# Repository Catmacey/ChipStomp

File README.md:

ChipStomp Guitar Effects Pedal
==============================

This is a digital guitar effects pedal based on the Arduino compatible Chipkit DP32 platform.
The project is a merging of a ChipKit DP32 with an Open Music Labs Stompshield in a custom build PCB.

The Chipkit is an arduino compatible platform powered by a 32bit Microchip PIC processor running at 40Mhz with 32Kb RAM and 128Kb flash.  

UPDATE: There is a [3d printable case available for this project](https://github.com/Catmacey/ChipStompCase). 

The project is relatively simple in that it limits itself to using the PIC's internal RAM, built in 10bit ADC and utilizes two 8bit PWMs to form a single 16bit output.  Also included is a 128x64px 1.3" OLED to provide a nice user interface.

Currently the following effects are completed.
- **Flanger** : Classic wobbly tape effect.

- **Tremolo** : Low frequency modulation of the source audio.

- **Pitch shift** : Change the pitch (up or down) of the source audio without changing the playback speed.

- **Echo/Delay** : A simple lo-fi delay (700ms Max) that when combined with a bit of analogue feedback provides a nice echo.

- **Bitcrusher** : Reduces the sample rate by ratios down to 1/64 of the source rate, also reduces the bit-depth to create some nice messy sounds.

You can have all or just some of these effect running at the same time with each passing its output onto the next effects input. 

[More information is available on my blog.](http://catmacey.wordpress.com/tag/chipstomp/)

Copyright (C) 2014 Matt Casey : catmacey.com
This program is free software: you can redistribute it and/or modify it under the terms of the GNU General Public License as published by the Free Software Foundation, either version 3 of the License, or (at your option) any later version.
	
This program is distributed in the hope that it will be useful, but WITHOUT ANY WARRANTY; without even the implied warranty of MERCHANTABILITY or FITNESS FOR A PARTICULAR PURPOSE.  See the GNU General Public License for more details.

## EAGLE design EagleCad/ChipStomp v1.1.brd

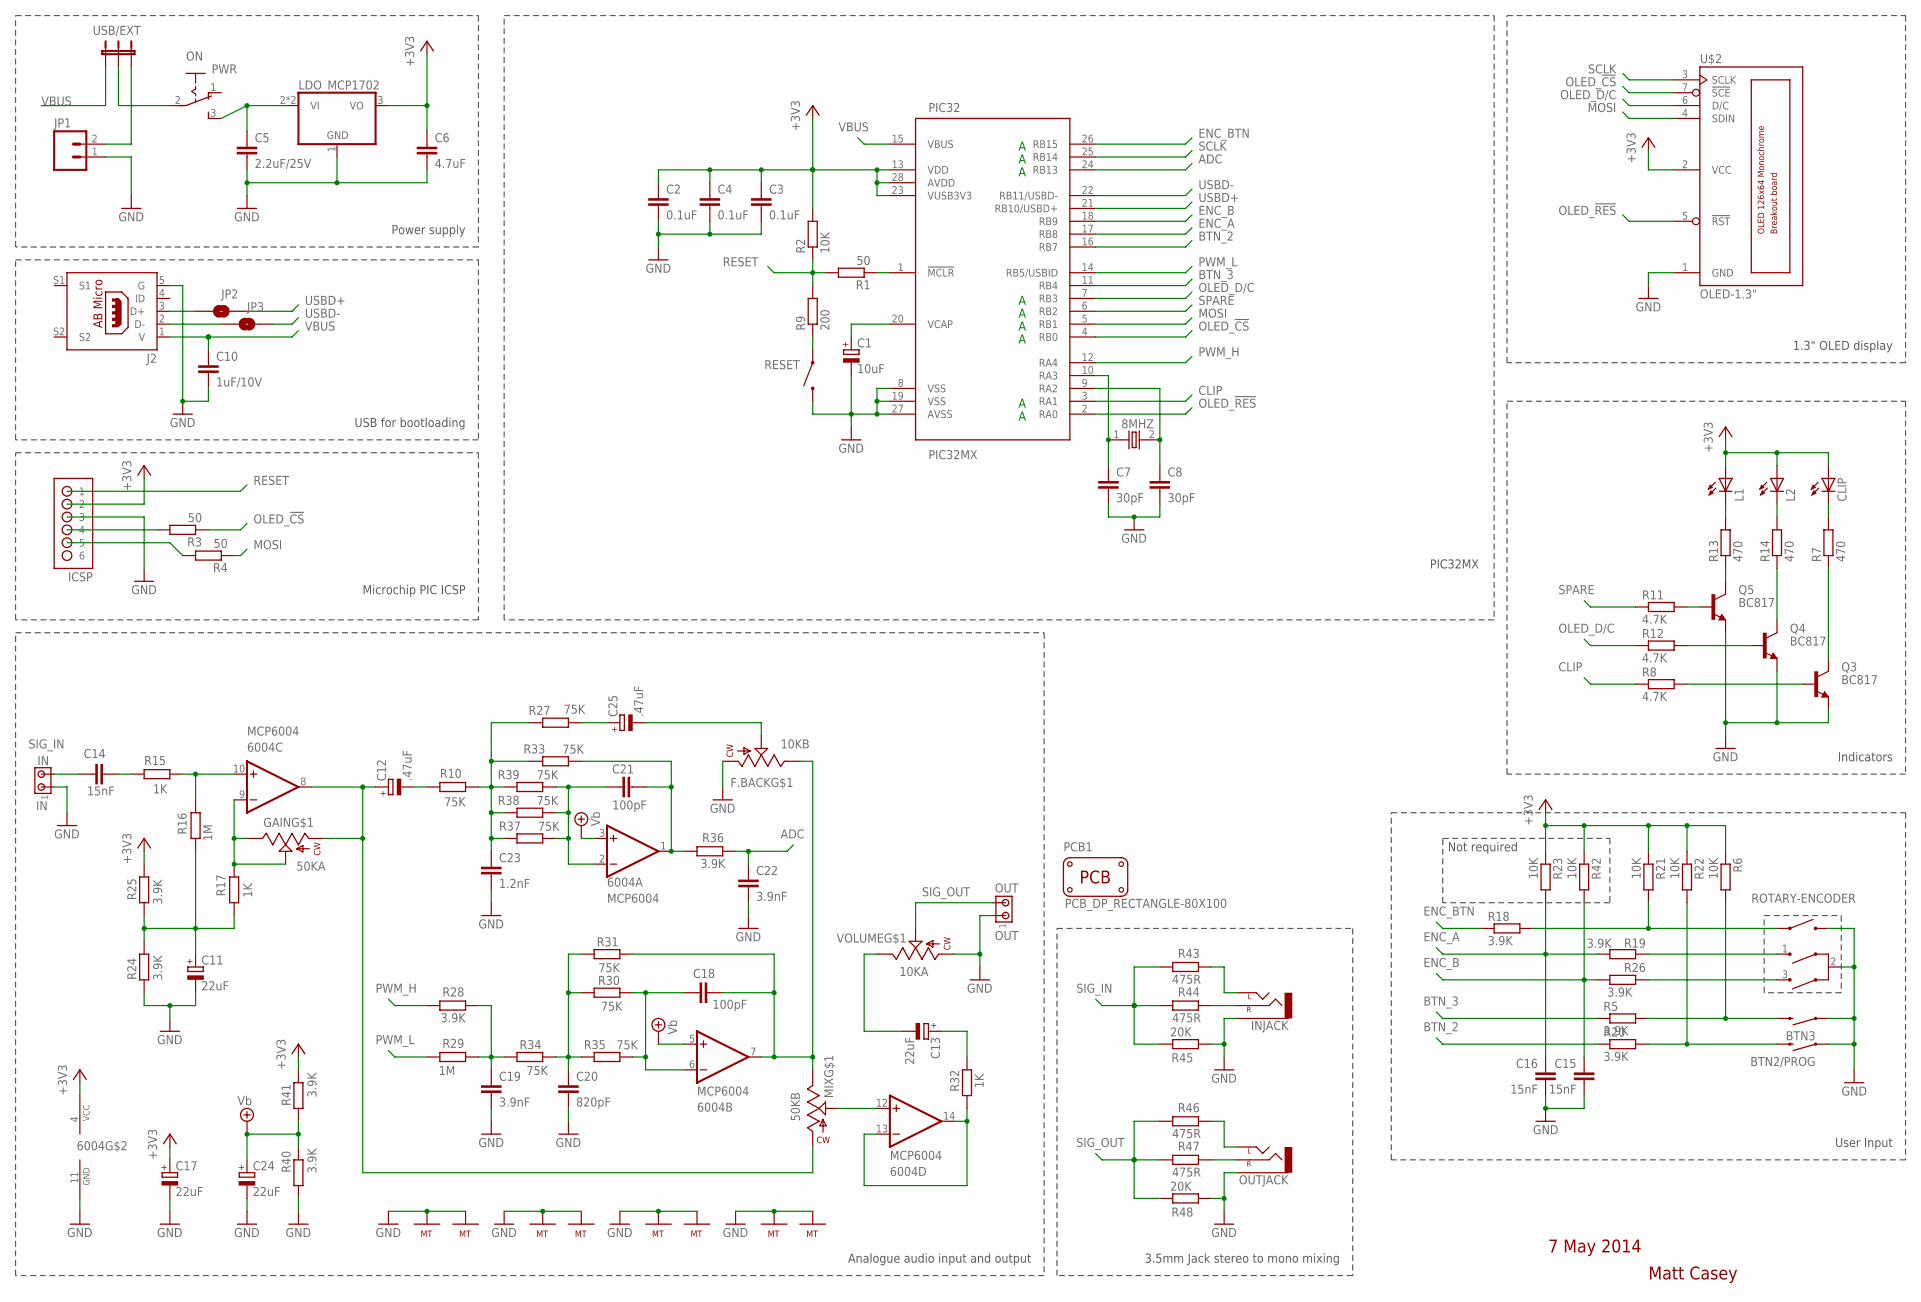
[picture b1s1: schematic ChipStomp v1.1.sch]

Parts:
8MHZ: OSC-XTAL-HC-49U-SMD; HC-49U
6004: MCP6004; SO-14
BTN2/PROG, BTN3: SWITCH-MOMENTARY-212MM; TACTILE-PTH-12MM
C1: 10uF; A/3216-18R
C2, C3, C4: 0.1uF; C0805K
C5: 2.2uF/25V; C0805K
C6: 4.7uF; C0805K
C7, C8: 30pF; C0805K
C10: 1uF/10V; C0805K
C11, C13, C17, C24: 22uF; 153CLV-0505
C12, C25: .47uF; 153CLV-0405
C14, C15, C16: 15nF; C0805K
C18, C21: 100pF; C0805K
C19, C22: 3.9nF; C0805K
C20: 820pF; C0805K
C23: 1.2nF; C0805K
CLIP: LED-0805; LED-805
F.BACK: 10KB; POT/SINGLE/PANASONIC/VERT
GAIN: 50KA; POT/SINGLE/PANASONIC/VERT
ICSP: No Load; HDR-1X6_OFFSET
IN: IN; JMP/2P/SIP
INJACK: AUDIO-JACKPTH; STEREO_JACK3.5MM_PTH
J2: US-AB-MICRO-TH; WMRU2AB-05FLB2DSR-4.0
JP1: M023.5MM; SCREWTERMINAL-3.5MM-2
JP2, JP3: Straight Male; SJ_2S-TRACE
L1, L2: LED-0805; LED-805
MIX: 50KB; POT/SINGLE/PANASONIC/VERT
ON: PWR; DX_MINI_SPDT_VERTICAL
OUT: OUT; JMP/2P/SIP
OUTJACK: AUDIO-JACKPTH; STEREO_JACK3.5MM_PTH
PCB1: PCB_DP_RECTANGLE-80X100; DP10080_V1
PIC32: PIC32MX; SO-28
Q3, Q4, Q5: BC817; SOT23-BEC
R1, R3, R4: 50; R0805
R2, R6, R21, R22, R23, R42: 10K; R0805
R5, R18, R19, R20, R24, R25, R26, R28, R36, R40, R41: 3.9K; R0805
R7, R13, R14: 470; R0805
R8, R11, R12: 4.7K; R0805
R9: 200; R0805
R10, R27, R30, R31, R33, R34, R35, R37, R38, R39: 75K; R0805
R15, R17, R32: 1K; R0805
R16, R29: 1M; R0805
R43, R44, R46, R47: 475R; R0805
R45, R48: 20K; R0805
RESET: TINY_TACTILEPTH; TINY_TACTILE_PTH
SW1: ROTARY-ENCODER; SURE
U$2: OLED-1.3"; OLED-130-BREAKOUT_2HOLES
U$3: LDO_MCP1702; SOT89
USB/EXT: JUMPER-3PTH; 1X03
VOLUME: 10KA; POT/SINGLE/PANASONIC/VERT

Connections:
+3V3: 6004.4 (VCC), C2.1, C3.1, C4.1, C6.1, C17.+, CLIP.A, ICSP.2, L1.A, L2.A, PIC32.13 (VDD), PIC32.23 (VUSB3V3), PIC32.28 (AVDD), R2.2, R6.1, R21.1, R22.1, R23.1, R25.1, R41.1, R42.1, U$2.2 (VCC), U$3.3 (VO)
ADC: C22.1, PIC32.24 (RB13), R36.1
BTN_2: PIC32.16 (RB7), R20.1
BTN_3: PIC32.11 (RB4), R5.1
CLIP: PIC32.3 (RA1), R8.1
ENC_A: C16.1, PIC32.17 (RB8), R19.1, R23.2
ENC_B: C15.1, PIC32.18 (RB9), R26.1, R42.2
ENC_BTN: PIC32.26 (RB15), R18.1
GND: 6004.11 (GND), BTN2/PROG.1, BTN3.1, C1.-, C2.2, C3.2, C4.2, C5.2, C6.2, C7.2, C8.2, C10.2, C11.-, C15.2, C16.2, C17.-, C19.2, C20.2, C22.2, C23.2, C24.-, F.BACK.P$1 (1), F.BACK.P$4 (MT), F.BACK.P$5 (MT), GAIN.P$4 (MT), GAIN.P$5 (MT), ICSP.3, IN.1, INJACK.S (SLEEVE), INJACK.S@1 (SLEEVE), J2.5 (G), JP1.1, MIX.P$4 (MT), MIX.P$5 (MT), OUT.1, OUTJACK.S (SLEEVE), OUTJACK.S@1 (SLEEVE), PIC32.8 (VSS), PIC32.19 (VSS), PIC32.27 (AVSS), Q3.E, Q4.E, Q5.E, R24.2, R40.2, R45.2, R48.2, RESET.2 (B), SW1.2 (COMMON), SW1.A (B), U$2.1 (GND), U$3.1 (GND), VOLUME.P$1 (1), VOLUME.P$4 (MT), VOLUME.P$5 (MT)
MOSI: PIC32.5 (RB1), R4.1, U$2.4 (SDIN)
unnamed: PIC32.1 (!MCLR), R1.1
unnamed: BTN3.3 (2), R5.2, R6.2
unnamed: Q3.C, R7.1
unnamed: Q3.B, R8.2
unnamed: CLIP.C, R7.2
unnamed: INJACK.L (LEFT), INJACK.L@1 (LEFT), R43.1
unnamed: INJACK.R (RIGHT), R44.1
unnamed: ON.2, USB/EXT.2
unnamed: OUTJACK.L (LEFT), OUTJACK.L@1 (LEFT), R46.1
unnamed: R9.1, RESET.1 (A)
unnamed: C1.+, PIC32.20 (VCAP)
unnamed: OUTJACK.R (RIGHT), R47.1
unnamed: C14.2, R15.2
unnamed: JP1.2, USB/EXT.3
unnamed: 6004.10 (+IN), R15.1, R16.2
unnamed: Q5.B, R11.2
unnamed: Q5.C, R13.1
unnamed: Q4.C, R14.1
unnamed: Q4.B, R12.2
unnamed: 6004.8 (OUT), C12.+, GAIN.P$1 (1), MIX.P$1 (1)
unnamed: J2.2 (D-), JP3.1
unnamed: 6004.9 (-IN), GAIN.P$2 (2), GAIN.P$3 (3), R17.2
unnamed: L1.C, R13.2
unnamed: L2.C, R14.2
unnamed: C12.-, R10.2
unnamed: R18.2, R21.2, SW1.B (A)
unnamed: BTN2/PROG.3 (2), R20.2, R22.2
unnamed: C23.1, R10.1, R27.2, R33.2, R37.2, R38.2, R39.2
unnamed: 6004.2 (-IN), C21.1, R37.1, R38.1, R39.1
unnamed: 6004.1 (OUT), C21.2, R33.1, R36.2
unnamed: C11.+, R16.1, R17.1, R24.1, R25.2
unnamed: C19.1, R28.1, R29.1, R34.2
unnamed: C20.1, R30.2, R31.2, R34.1, R35.2
unnamed: 6004.6 (-IN), C18.1, R30.1, R35.1
unnamed: C25.+, R27.1
unnamed: 6004.7 (OUT), C18.2, F.BACK.P$3 (3), MIX.P$3 (3), R31.1
unnamed: C13.+, R32.1
unnamed: C13.-, VOLUME.P$3 (3)
unnamed: R19.2, SW1.1 (SIG1)
unnamed: R26.2, SW1.3 (SIG2)
unnamed: C25.-, F.BACK.P$2 (2)
unnamed: 6004.12 (+IN), MIX.P$2 (2)
unnamed: 6004.13 (-IN), 6004.14 (OUT), R32.2
OLED_!CS: PIC32.4 (RB0), R3.1, U$2.7 (!SCE)
OLED_!RES: PIC32.2 (RA0), U$2.5 (!RST)
OLED_D/C: PIC32.7 (RB3), R12.1, U$2.6 (D/C)
OSC1/CLKI/RPA2/RA2: 8MHZ.2, C8.1, PIC32.9 (RA2)
OSC2/CLKO/RPA3/PMA0/RA3: 8MHZ.1, C7.1, PIC32.10 (RA3)
PGC: ICSP.5, R4.2
PGD: ICSP.4, R3.2
PWM_H: PIC32.12 (RA4), R28.2
PWM_L: PIC32.14 (RB5/USBID), R29.2
RESET: ICSP.1, R1.2, R2.1, R9.2
SCLK: PIC32.25 (RB14), U$2.3 (SCLK)
SIG_IN: C14.1, IN.2, R43.2, R44.2, R45.1
SIG_OUT: OUT.2, R46.2, R47.2, R48.1, VOLUME.P$2 (2)
SPARE: PIC32.6 (RB2), R11.1
USBD+: J2.3 (D+), JP2.1, JP2.2, PIC32.21 (RB10/USBD+)
USBD-: JP3.2, PIC32.22 (RB11/USBD-)
VBUS: C10.1, J2.1 (V), PIC32.15 (VBUS), USB/EXT.1
VIN: C5.1, ON.3 (S), U$3.2 (VI), U$3.4 (VI)
VREF: 6004.3 (+IN), 6004.5 (+IN), C24.+, R40.1, R41.2

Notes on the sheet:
User Input
Power supply
Indicators
3.5mm Jack stereo to mono mixing
Analogue audio input and output
USB for bootloading
Microchip PIC ICSP
1.3" OLED display
Matt Casey
PIC32MX
7 May 2014
Not required

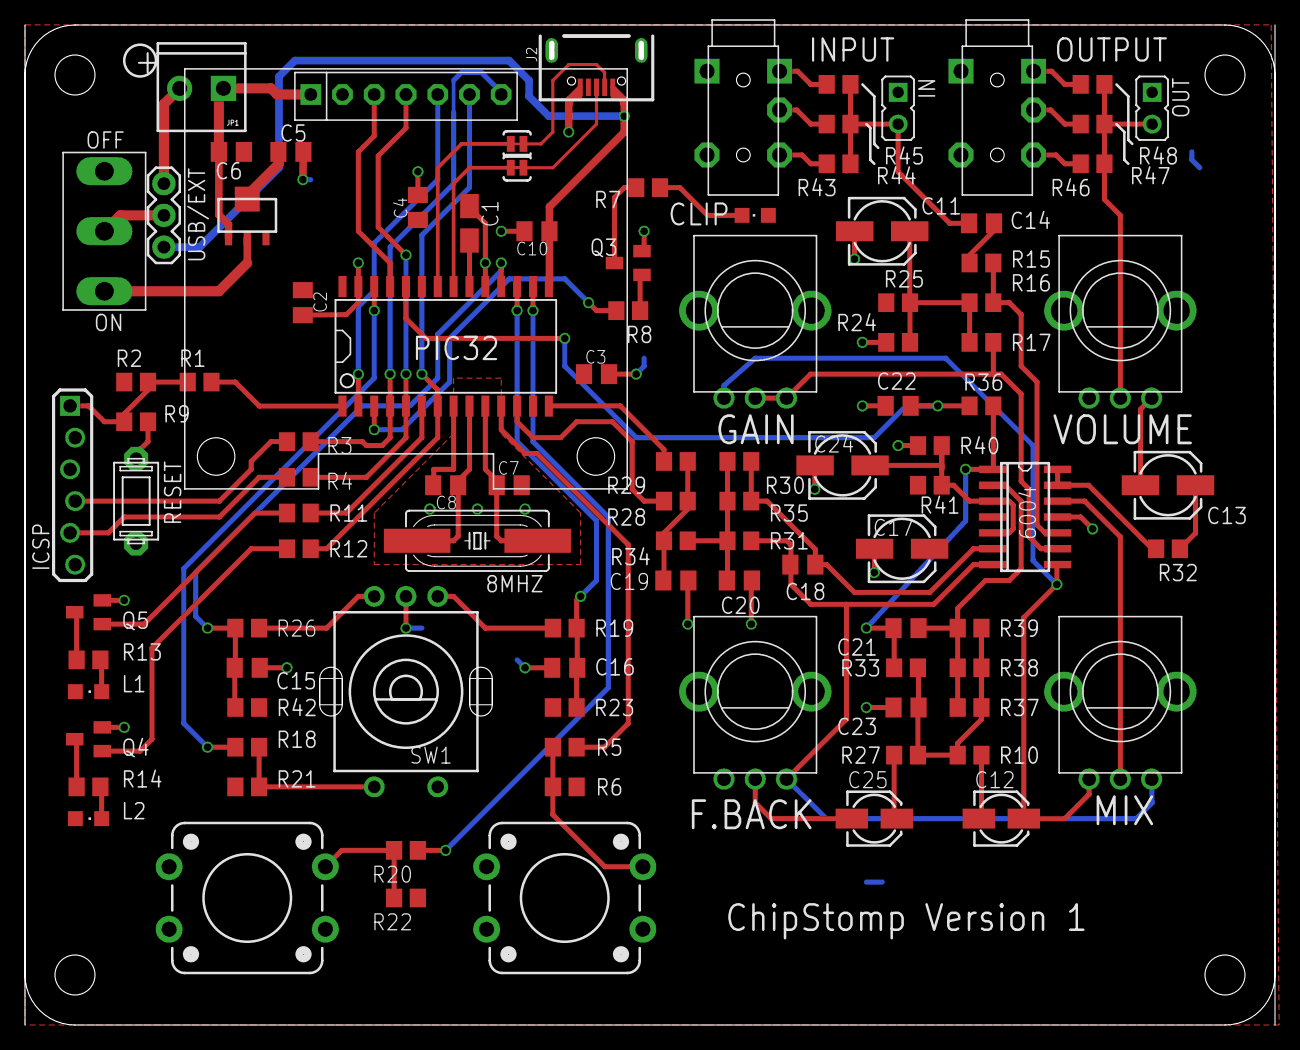
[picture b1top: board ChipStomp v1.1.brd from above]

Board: 2 copper layers, 100.0 x 80.0 mm, 103 parts (0 on the bottom side), 72 nets.

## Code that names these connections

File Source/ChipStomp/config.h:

/*
	Main header file
*/

#ifndef __Config__
#define __Config__

#include <stdint.h> 

// #define SAMPLERATE 44100    // Hz
// #define SAMPLETIME 0.02267 // Approx sample time in mS 
#define SAMPLERATE 40000
#define SAMPLETIME 0.025
// #define SAMPLERATE 32000  
// #define SAMPLETIME 0.03125
#define CLIPLEVEL 31000  // Full range is +32767 to -32767 but this is the level we light the LED at.
#define CLIPHARD 32767

// PIC port/pins
// PORT A
#define OLEDRES_BIT BIT_0  // RA0
#define CLIP_BIT    BIT_1  // RA1
// BIT_2 Osc
// BIT_3 Osc
#define DACHI_BIT   BIT_4  // RA4

// PORT B
// Outputs
#define OLEDCS_BIT  BIT_0
#define MOSI_BIT    BIT_1   // RB1
// BIT_2 Spare
#define OLEDDC_BIT  BIT_3   // RB3
#define DACLO_BIT   BIT_5   // RA5
#define SCLK_BIT    BIT_14

// Inputs
#define BTNSELECT_BIT BIT_4 // RB4
#define BTNEFFECT_BIT BIT_7 // RB7
#define ENCA_BIT BIT_8 // RB8
#define ENCB_BIT BIT_9 // RB9
#define ENCBTN_BIT BIT_15 // RB15

#define ENC_MASK ENCA_BIT | ENCB_BIT // Mask for encoder inputs
#define BTN_MASK BTNEFFECT_BIT | BTNSELECT_BIT | ENCBTN_BIT // Mask for buttons
#define INPUT_MASK ENC_MASK | BTN_MASK // Mask for all inputs

#define VUTICKLEN 16
#define VUTICKLEN_MASK 0x0f

// Some handy values for screen layout
#define DISP_FEAT_Y 20  // Start point for features area
#define DISP_FEAT_W 123 // MAx width of features area (allowing space for VU meter)
#define DISP_FEAT_INDENT 2  // Start point for features area

// Stupid Arduino pin numbers
#define OLED_RESET 9 // RA0 
#define DACL 0 // RB5 DAC Low byte
#define DACH 18 // RA4 DAC High byte
#define SPI_CLK 7 // RB14
#define OLED_CS 11 // RB0
#define OLED_DC 14 // RB3
#define SPI_MOSI 12 // RB1
#define _DSPI1_MOSI_PIN   12
// End of stupid Arduino pin numbers

#define SYS_FREQ 40000000 // PIC OSC frequency
#define GetSystemClock() SYS_FREQ
#define GetPeripheralClock()    (GetSystemClock() / (1 << OSCCONbits.PBDIV))

// This is used to store button state
// The Port the buttons are on is 16bit but the 
// in our case all the buttons are on the lower byte
typedef union {
  uint8_t complete;
  struct {
    unsigned :4;
    unsigned select:1;
    unsigned :1;
    unsigned :1;
    unsigned effect:1;
  };
} ButtonState_t;

// This is used to store the input
typedef struct {
  struct {
    int16_t value; // Accumulated value of encoder input. Set to 0 once actioned
    uint8_t state; // Current state, used in ISR decoding
  } encoder;
  ButtonState_t btn_state; // 1 = pressed
  ButtonState_t btn_diff; // 1 = different from last time
  uint32_t btn_timer; // Could use this to determine how long since last input...
} InputState_t;

// This is used to store the input and output VU Meter
typedef struct {
  int16_t input[VUTICKLEN];
  int16_t output[VUTICKLEN];
  uint8_t peak_in;
  uint8_t peak_out;
  uint8_t tick;
} VUMeter_t;


// Sinewave : 1024 value array of signed 16bit integers
const int16_t g_sinewave[] = {
  #include <sinetable.inc>
};

// Splash screen
const uint8_t g_splashscreen[] = {
  #include <splashscreen.inc>
};


// Returns the percentage value of value between the min and max range
extern float percentage(uint16_t value, uint16_t max, uint16_t min);

#endif

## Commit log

2014-05-29 Initial project creation.
    First upload of project description and Eagle Cad schematics and board
    layout
2014-05-29 Improved project readme
2014-05-29 Fixed broken markup
2014-09-28 First upload of Source code and libraries.
2014-09-29 Updated readme
    Provided a bit more info about the project in the readme.
2014-10-10 Added bootloader HEX
    Added compiled HEX of the ChipStomp specific bootloader.
    It's a modified Chipkit DP32 bootloader with the buttons configured as
    pulled high - active low, rather than pulled low - active high.
    Also added the BoardConfig.h from the Chipkit bootloader project
    modified to include the Chipstomp board definition.
2014-11-16 Added licence text to readme
2015-03-25 Changed sample rate to 40k
    Also a few updates to comments and minor changes.
2015-10-08 Updated to use multi-font GFX lib
    Modified as an example of using newly modified GFX lib to display two
    different fonts. DejaVuSans 12 for headers and LiberationSans 10 for
    body.

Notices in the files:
parts and their libraries:
SparkFun: Licensing: CC v3.0 Share-Alike You are welcome to use this library for commercial purposes.
